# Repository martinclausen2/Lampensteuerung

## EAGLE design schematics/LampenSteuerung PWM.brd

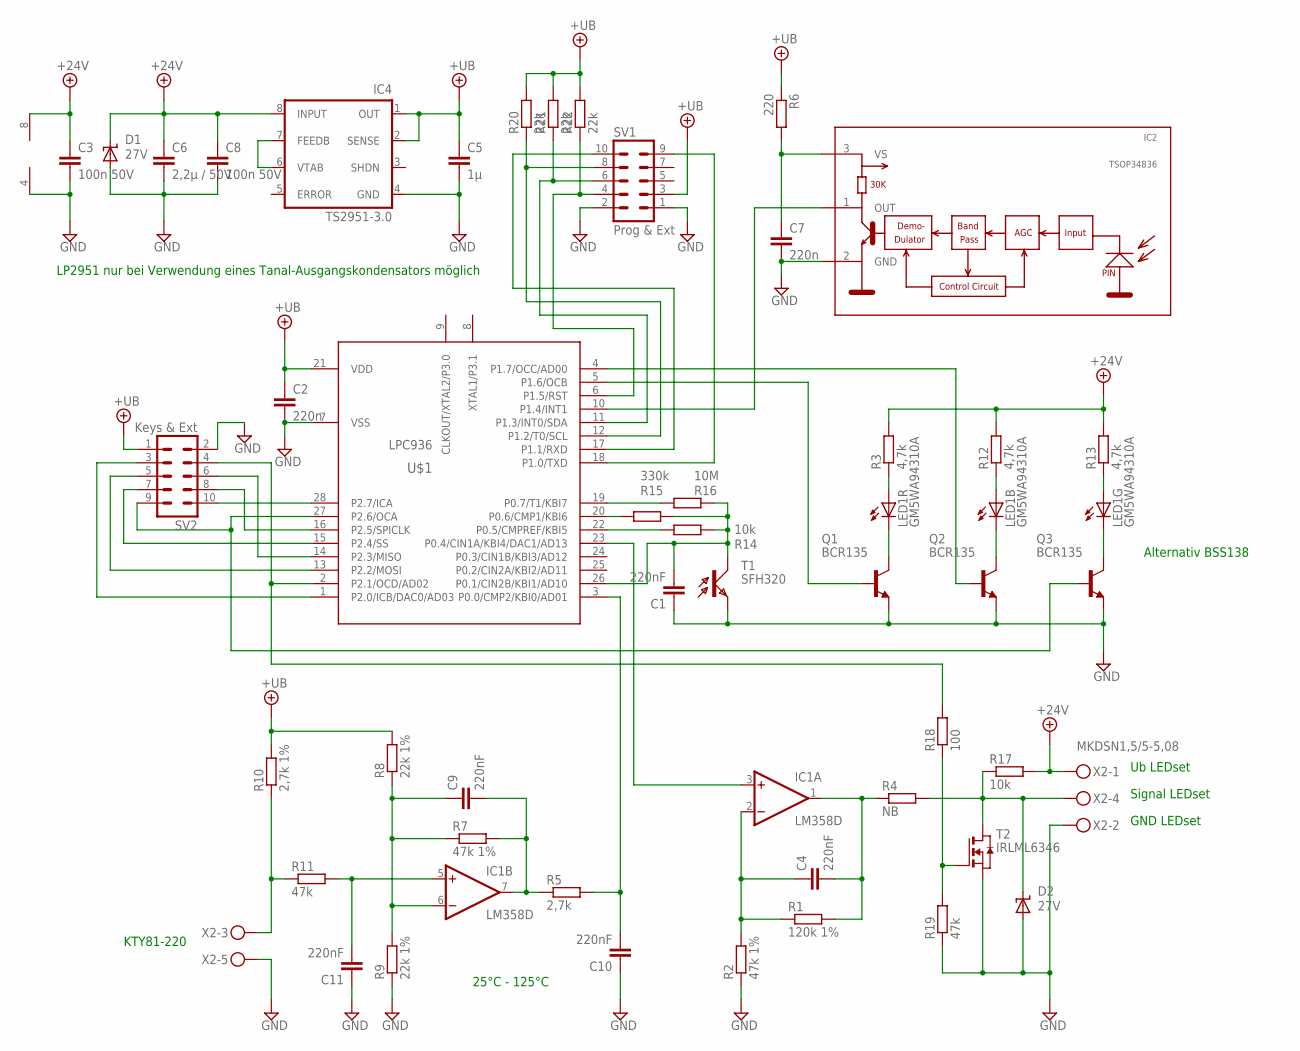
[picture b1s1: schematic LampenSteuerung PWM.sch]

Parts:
C1, C4, C9, C10, C11: 220nF; C0603
C2, C7: 220n; C0603
C3, C8: 100n 50V; C0603
C5: 1µ; C0805
C6: 2,2µ / 50V; C1206
D1, D2: 27V; SMBJ
IC1: LM358D; SO08
IC2: TSOP34836; TSOP348
IC4: TS2951-3.0; SO-08
LED1: GM5WA94310A
Q1, Q2, Q3: BCR135; SOT23-BEC
R1: 120k 1%; R0805
R2, R7: 47k 1%; R0805
R3, R12, R13: 4,7k; R0805
R4: NB; R0805
R5: 2,7k; R0805
R6: 220; R0805
R8, R9: 22k 1%; R0805
R10: 2,7k 1%; R0805
R11, R19: 47k; R0805
R14, R17: 10k; R0805
R15: 330k; R0805
R16: 10M; R0805
R18: 100; R0805
R20, R21, R22: 22k; R0805
SV1: Prog & Ext; MA05-2
SV2: Keys & Ext; MA05-2
T1: SFH320; PLCC2
T2: IRLML6346; SOT-23
U$1: LPC936; TSSOP28
X2: MKDSN1,5/5-5,08

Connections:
+12V: C3.1, C6.1, C8.1, D1.C, IC1.8 (V+), IC4.8 (INPUT), R3.2, R12.2, R13.2, R17.2, X2.1
+UB: C2.1, C5.1, IC4.1 (OUT), IC4.2 (SENSE), R6.1, R8.2, R10.2, R20.2, R21.2, R22.2, SV1.3, SV2.1, U$1.21 (VDD)
GND: C1.1, C2.2, C3.2, C5.2, C6.2, C7.2, C8.2, C10.1, C11.1, D1.A, D2.A, IC1.4 (V-), IC2.2 (GND), IC4.4 (GND), Q1.E, Q2.E, Q3.E, R2.1, R9.1, R19.1, SV1.1, SV1.2, SV2.2, T1.C (E), T2.2 (S), U$1.7 (VSS), X2.2, X2.5
unnamed: IC4.6 (VTAB), IC4.7 (FEEDB)
unnamed: IC2.1 (OUT), U$1.10 (P1.4/INT1)
unnamed: IC1.3 (+IN), U$1.23 (P0.4/CIN1A/KBI4/DAC1/AD13)
unnamed: C9.1, IC1.6 (-IN), R7.1, R8.1, R9.2
unnamed: LED1.5 (C), Q1.C
unnamed: C4.2, IC1.1 (OUT), R1.2, R4.1
unnamed: C4.1, IC1.2 (-IN), R1.1, R2.2
unnamed: SV1.10, U$1.17 (P1.1/RXD)
unnamed: D2.C, R4.2, R17.1, T2.1 (D), X2.4
unnamed: C7.1, IC2.3 (VS), R6.2
unnamed: SV1.9, U$1.18 (P1.0/TXD)
unnamed: LED1.6 (C), Q2.C
unnamed: R22.1, SV1.4, U$1.6 (P1.5/RST)
unnamed: LED1.1 (A), R12.1
unnamed: R20.1, SV1.8, U$1.12 (P1.2/T0/SCL)
unnamed: R21.1, SV1.6, U$1.11 (P1.3/INT0/SDA)
unnamed: C10.2, R5.2, U$1.3 (P0.0/CMP2/KBI0/AD01)
unnamed: R10.1, R11.1, X2.3
unnamed: C9.2, IC1.7 (OUT), R5.1, R7.2
unnamed: C11.2, IC1.5 (+IN), R11.2
unnamed: LED1.2 (A), R3.1
unnamed: SV2.3, U$1.1 (P2.0/ICB/DAC0/AD03)
unnamed: R18.2, SV2.4, U$1.2 (P2.1/OCD/AD02)
unnamed: SV2.5, U$1.13 (P2.2/MOSI)
unnamed: SV2.6, U$1.14 (P2.3/MISO)
unnamed: SV2.7, U$1.15 (P2.4/SS)
unnamed: SV2.8, U$1.16 (P2.5/SPICLK)
unnamed: Q3.B, SV2.9, U$1.27 (P2.6/OCA)
unnamed: SV2.10, U$1.28 (P2.7/ICA)
unnamed: LED1.3 (A), R13.1
unnamed: LED1.4 (C), Q3.C
unnamed: Q1.B, U$1.5 (P1.6/OCB)
unnamed: Q2.B, U$1.4 (P1.7/OCC/AD00)
unnamed: C1.2, R14.1, R15.1, R16.1, T1.A (C), U$1.26 (P0.1/CIN2B/KBI1/AD10)
unnamed: R16.2, U$1.19 (P0.7/T1/KBI7)
unnamed: R15.2, U$1.20 (P0.6/CMP1/KBI6)
unnamed: R14.2, U$1.22 (P0.5/CMPREF/KBI5)
unnamed: R18.1, R19.2, T2.3 (G)

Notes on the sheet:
LP2951 nur bei Verwendung eines Tanal-Ausgangskondensators möglich
Signal LEDset
Ub LEDset
GND LEDset
KTY81-220
25°C - 125°C
Alternativ BSS138

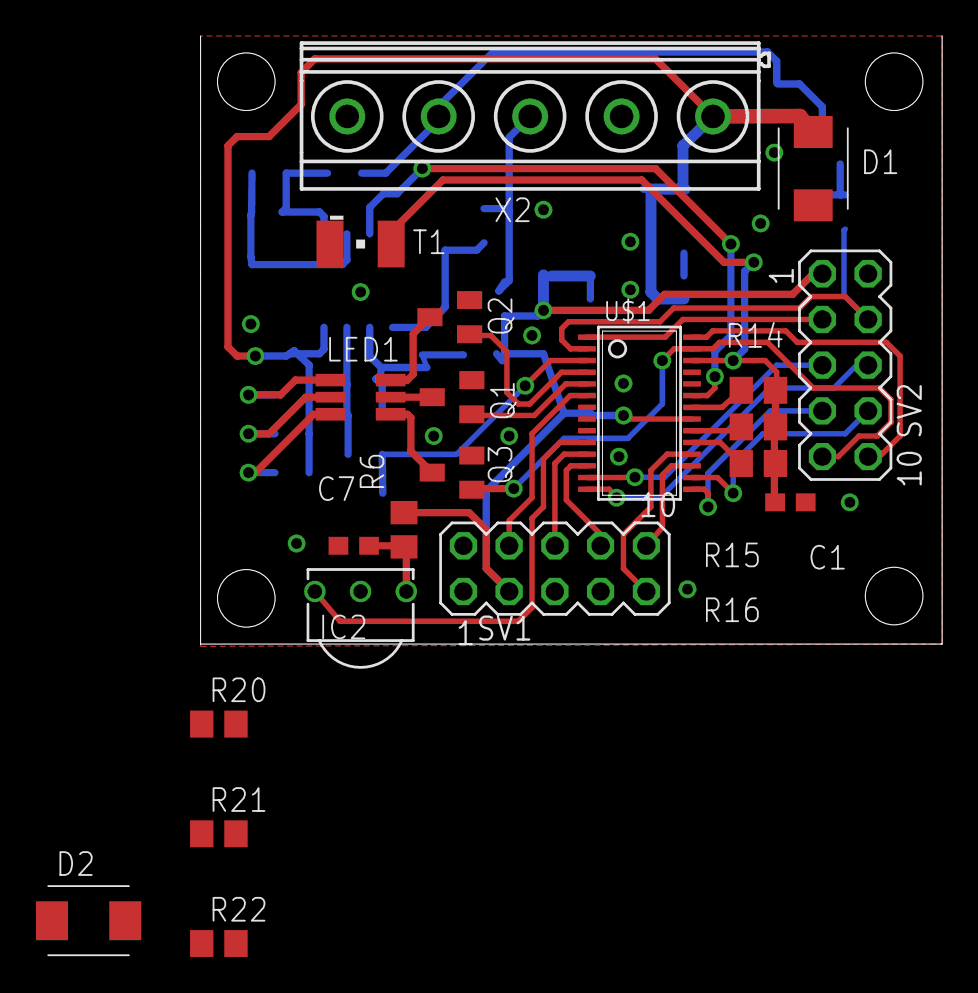
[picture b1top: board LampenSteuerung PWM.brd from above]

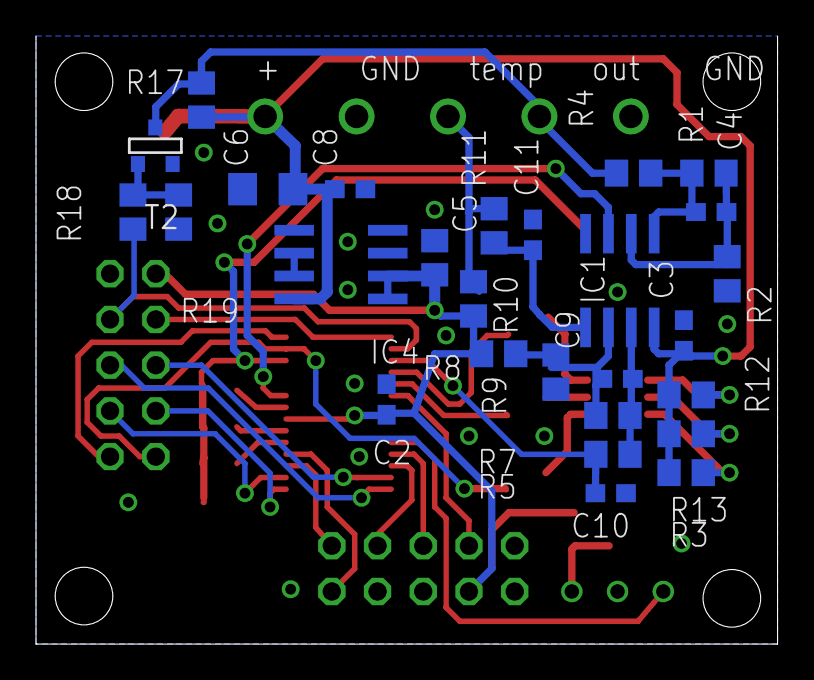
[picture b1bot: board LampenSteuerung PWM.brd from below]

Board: 2 copper layers, 41.2 x 33.8 mm, 48 parts (27 on the bottom side), 41 nets.

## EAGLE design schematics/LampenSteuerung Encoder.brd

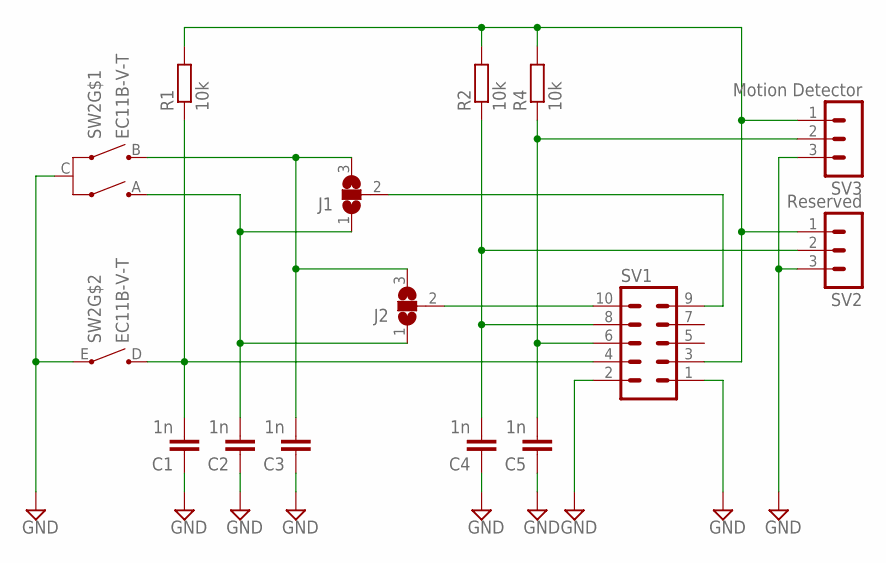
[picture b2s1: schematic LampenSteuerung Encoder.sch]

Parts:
C1, C2, C3, C4, C5: 1n; C0603K
J1, J2: SJ2W; SJ_2
R1, R2, R4: 10k; R0805
SV1: MA05-2
SV2: Reserved; MA03-1
SV3: Motion Detector; MA03-1
SW2: EC11B-V-T; EC11B-V

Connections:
GND: C1.1, C2.1, C3.1, C4.1, C5.1, SV1.1, SV1.2, SV2.3, SV3.3, SW2.C, SW2.E
unnamed: C1.2, R1.1, SV1.4, SW2.D
unnamed: C2.2, J1.1, J2.1, SW2.A
unnamed: C3.2, J1.3, J2.3, SW2.B
unnamed: R1.2, R2.2, R4.2, SV1.3, SV2.1, SV3.1
unnamed: C5.2, R4.1, SV1.6, SV3.2
unnamed: C4.2, R2.1, SV1.8, SV2.2
unnamed: J1.2, SV1.9
unnamed: J2.2, SV1.10

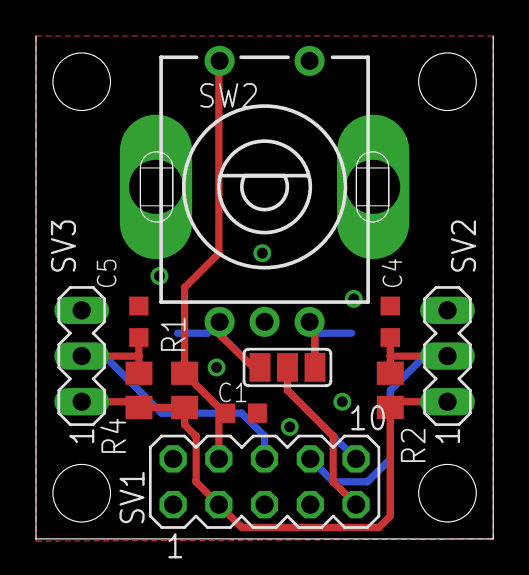
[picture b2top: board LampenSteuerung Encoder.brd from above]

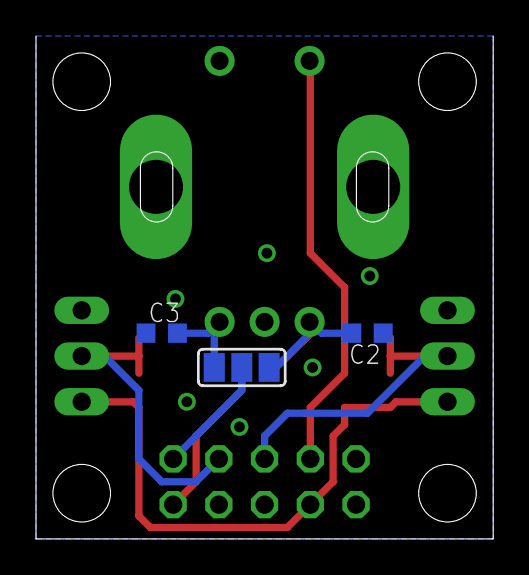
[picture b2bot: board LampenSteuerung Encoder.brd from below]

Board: 2 copper layers, 25.4 x 27.9 mm, 14 parts (3 on the bottom side), 9 nets.

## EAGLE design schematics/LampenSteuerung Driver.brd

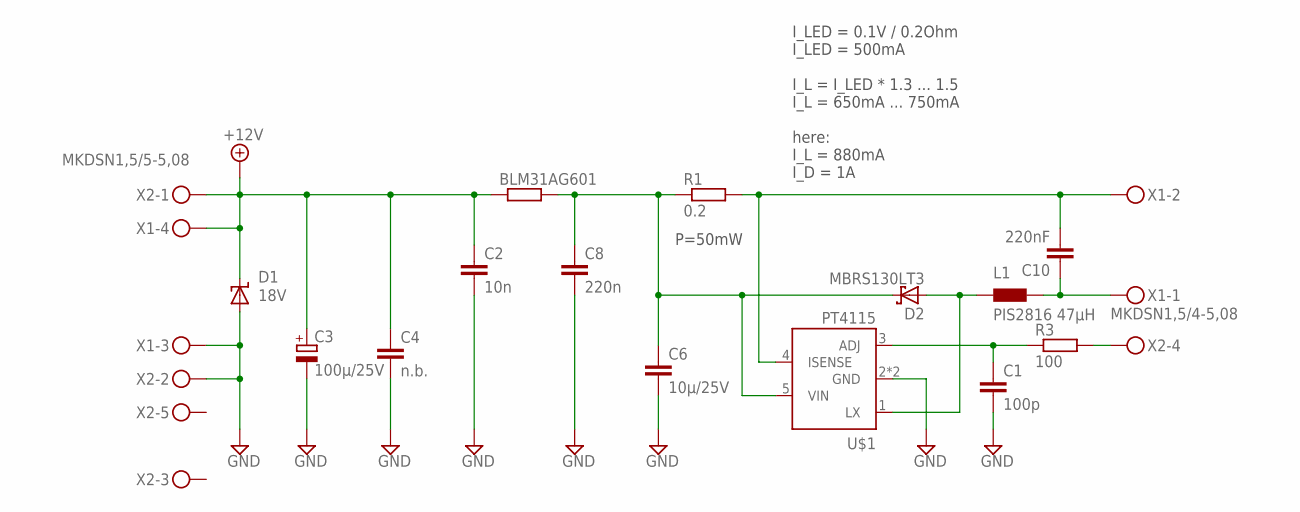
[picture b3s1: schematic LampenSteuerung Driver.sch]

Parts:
BLM31AG601: R-EU_R1206; R1206
C1: 100p; C0603
C2: 10n; C0603
C3: 100µ/25V; E2,5-6
C4: n.b.; C1210
C6: 10µ/25V; C1206
C8: 220n; C0603
C10: 220nF; C0603
D1: 18V; SMBJ
D2: MBRS130LT3; SMB
L1: PIS2816 47µH; PIS2816
R1: 0.2; R1206
R3: 100; R1206
U$1: PT4115; SOT89-5
X1: MKDSN1,5/4-5,08
X2: MKDSN1,5/5-5,08

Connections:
+12V: BLM31AG601.1, C2.1, C3.+, C4.1, D1.C, X1.4, X2.1
GND: C1.2, C2.2, C3.-, C4.2, C6.2, C8.2, D1.A, U$1.2 (GND), U$1.2.1 (GND), X1.3, X2.2
unnamed: C1.1, R3.1, U$1.3 (ADJ)
unnamed: C10.2, R1.2, U$1.4 (ISENSE), X1.2
unnamed: C10.1, L1.P$2, X1.1
unnamed: D2.A, L1.P$1, U$1.1 (LX)
unnamed: R3.2, X2.4
unnamed: BLM31AG601.2, C6.1, C8.1, D2.C, R1.1, U$1.5 (VIN)

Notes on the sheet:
I_LED = 0.1V / 0.2Ohm I_LED = 500mA I_L = I_LED * 1.3 ... 1.5 I_L = 650mA ... 750mA here: I_L = 880mA I_D = 1A
P=50mW

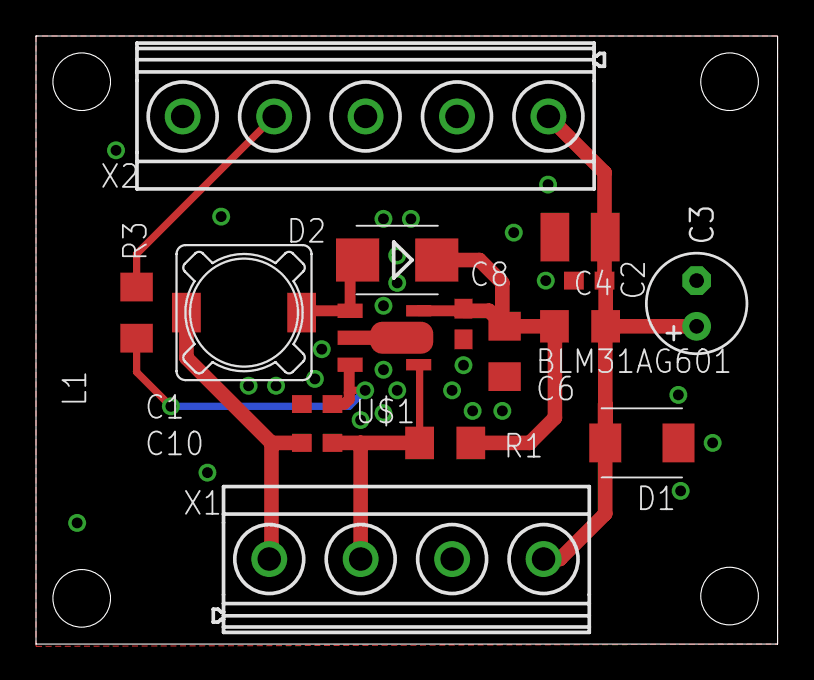
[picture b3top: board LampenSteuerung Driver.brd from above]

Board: 2 copper layers, 41.2 x 33.8 mm, 16 parts (0 on the bottom side), 8 nets.

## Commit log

2013-10-11 Initial Upload
2013-10-11 added schematics and PCB added mechanics
2013-10-11 first stable upload
2013-10-17 - finalized layout - moved to eagle 6.5
2013-11-03 - added dynamic PWM frequency selection - extended options menu by brightness offset and min brightness - increased dimming frequency to 40Hz
2013-11-03 - fix ZXLD1374 case
2013-12-09 - added fill & 2nd line function to lcd driver => code clean-up - added user feedback on key pressed - fixed missing pause between IR commands in all go standby - added fade in to snooze end menu - p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
2013-12-09 - minor code clean-up
2014-02-03 - add: option to cancel key press - add: optional acoustic signal to acknowledge key press - add: ZXLD1374 support via compiler switch
2014-02-05 -fix: missing key acknowledge
2014-02-22 - changed to LED driver ZXLD1374 as a default - fixed output configuration of PWM Pins - added "sample beep" during beep volume adjustment, fixed volume enumeration
2014-03-10 - improved placement of IR-LED, IR-Receiver, Photodiode - removed unused devices
2014-03-11 added 3D-model of mechanics for left and right lamp and description
2014-09-04 filled Lampensteuerung branch
2014-09-07 added motion detector signal handling added LCD option via #define
2014-09-07 fix alarm
2014-09-07 fix spelling fix time out for acoustic alarm
2014-09-12 fix missing off slope at analogue output fix spike during analogue output on fix timing
2014-09-14 added time slots for main loop fixed timing other small fixes
2014-09-14 fix comment
2014-09-16 fix inverted PWM output
2014-10-08 fixed missing offset for output cleaned RC5 code, added function for number buttons fixed comments
2014-10-09 reduce power consumption of MCU
2014-10-12 add remote control number block functionality code clean-up
2015-04-06 fixed display error
2015-05-18 added missing pull-up resistors added wire pads for output shifted some components slightly to ease mounting
2015-09-24 - option to compile for noninverted PWM output for direct drive of LEDs - flash LED if brightness limits are reached - added comments, fixed spelling
2015-09-25 - fixed led min max led flash - increased encoder acceleration
2015-10-01 - optimize encoder settings - fix limit led signal in options
2015-10-01 - optimize encoder settings further
2015-10-03 - fixed flicker of output - fixed overflow in Encoder.c - use lower limit instead of zero for brightness
2015-10-03 - fix lower limit for brightness
2015-10-05 - added version for direct PWM control
2016-03-12 added schematics
2016-03-12 added driver and encoder pcb
2016-07-14 added dimming function for standby status led improved options status led (cleaner code, better usablity)
2019-01-25 update to SDCC 3.8 added sleep function
2019-01-28 prolonged fade out added option to switch fade out off
2021-03-28 adjust ADC settings for more precise ambient light measurement
2022-11-05 updated to SDCC 4.2.0 prolonged key press time to enter option menu to avoid unwanted entry of the options menu
2022-11-06 fix key press duration update version
